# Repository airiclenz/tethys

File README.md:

<div align="center">

**A self-hosted, multi-channel automatic plant-watering system.**
</div>

Battery-powered wireless soil-moisture sensors report to a Raspberry Pi master
over a 2.4 GHz nRF24 radio link. The master decides when to water, drives the
pumps/valves, and serves a real-time web dashboard — all on your own LAN, no
cloud.

## Part 1 — What Tethys is and how to use it

### The big picture

Tethys has two kinds of hardware:

1. **Sensor nodes** (one per plant/pot, up to 5) — a battery-powered ATtiny84
   board with a capacitive soil-moisture probe and an nRF24L01+ radio. Each node
   sleeps almost all the time, wakes on a configurable interval, measures soil
   moisture and battery voltage, transmits a reading, and goes back to sleep.
   Designed to run for months on a single charge (~9 µA while sleeping).

2. **The master** — a Raspberry Pi with a custom HAT carrying the matching
   nRF24L01+ radio plus pump/valve driver outputs. The master listens for sensor
   readings, stores them, and when a channel's soil drops below its trigger
   threshold it runs that channel's pump (or opens its valve) for a configured
   duration. It also serves the web UI you use to configure and monitor
   everything.

```
   ┌─────────────┐   nRF24 2.4GHz      ┌──────────────────────────────────┐
   │ Sensor node │  (250kbps, 8-byte   │         Raspberry Pi master      │
   │  ATtiny84   │   versioned frames) │                                  │
   │  + moisture │ ◄──── reading ────► │  core daemon ─► pump/valve GPIO  │
   │  + nRF24    │      config ◄────   │              │                   │
   │  (battery)  │                     │  Django API (SQLite) ◄─► web UI  │
   └─────────────┘                     └──────────────┬───────────────────┘
        × up to 5                                     │  HTTP / WebSocket
                                                      ▼
                                              Your browser / phone
```

Each **channel** (1..5) pairs one sensor node with one pump or valve output.
A channel knows its soil-moisture trigger %, its pump run duration, and how
often its sensor should measure.

### Repository layout

```
tethys/
├── code/
│   ├── master/            # Everything that runs on the Raspberry Pi
│   │   ├── core/          # The watering daemon (radio + pump control + action engine)
│   │   ├── api/           # Django REST API (the system's database + state)
│   │   ├── web/           # Django + Channels dashboard (browser UI)
│   │   ├── camera/        # Optional on-demand webcam snapshot service (USB/V4L2)
│   │   ├── watchdog/      # Daily service-restart / log-vacuum job
│   │   ├── globals/       # Shared config + git-ignored secrets
│   │   └── install/       # install.sh, systemd units, nginx configs
│   └── sensor/            # Arduino/PlatformIO firmware for the sensor nodes (the "wpw" project)
├── hardware/              # KiCad schematics + Gerbers for the Pi HAT and the sensor PCB
├── graphics/              # Logos, hardware labels, web-UI assets, renders
└── docs/                  # Audits, protocol review, hardening notes, handoffs
```

### Hardware

**Master — Raspberry Pi + "WaterPlant Pi" HAT** (`hardware/rpi hat/`).
GPIO assignments live in [`code/master/core/hardware.py`](code/master/core/hardware.py):

| Function          | BCM pin(s)            | Notes                                            |
|-------------------|-----------------------|--------------------------------------------------|
| Channel outputs   | `16, 19, 20, 26, 21`  | One per channel; `CHANNEL_COUNT = 5`             |
| Shared pump pin   | `6`                   | Energised together with a channel in **valve** mode |
| Water-level sensor| `4`                   |                                                  |
| nRF24 CE / CSN / IRQ | `22 / 0 / 17`      | SPI radio                                         |
| Status LED / Fan  | `14 / 15`             |                                                  |

A channel of type **pump** drives its own pin directly. A channel of type
**valve** drives its pin *and* the shared `PUMP` pin (one pump pushing water
through whichever valves are open); the pump pin is reference-counted so it
only drops once the last valve closes.

**Sensor node — "Sensor" PCB** (`hardware/sensor/`), firmware in `code/sensor/`:

- **MCU:** ATmega/ATtiny84 @ 8 MHz (PlatformIO `TX` build), deep-sleep
  `SLEEP_MODE_PWR_DOWN`, woken by the 8-second watchdog timer.
- **Radio:** nRF24L01+ on CE=8 / CSN=9, 250 kbps, CRC-8, auto-ACK.
- **Moisture:** capacitive probe excited by a ~500 kHz square wave (Timer0 on
  `PB2`), read on ADC `PA3`; calibration min/max stored in EEPROM.
- **Battery:** monitored on `A7` against the internal 1.1 V reference; below
  **3.2 V** the node sends a battery-alert frame instead of a normal reading.

### Install (on the Raspberry Pi)

```bash
sudo apt install git -y
git clone https://github.com/airiclenz/tethys.git tethys
cd tethys/code/master/install
./install.sh
```

The installer updates the OS, creates a Python venv, installs Redis + nginx,
runs the Django migrations, registers the systemd services, enables SPI, and
**reboots** (re-run `./install.sh --rebooted=true` afterward if you decline the
auto-reboot). On first run it generates a random **API key** into the
git-ignored `code/master/globals/secrets.py` and **prints it** — copy it.

Useful flags:
- `--debug=true` — developer install (also installs the TypeScript toolchain).
- `--allowed-hosts=tethys.<tailnet>.ts.net` — extra `ALLOWED_HOSTS` for remote
  (VPN) access. Alternatively (and preferred per-install), list the name in the
  git-ignored `code/master/globals/allowed_hosts.py` (copy `allowed_hosts.example.py`)
  — no reinstall needed, just restart the services. See
  [`docs/remote-access-hardening.md`](docs/remote-access-hardening.md).

After it's up: open `http://<pi-host>/` in a browser → **Settings** (top menu) →
paste the API key → Save. The key gates **every** request (reads included; only
the CORS `OPTIONS` preflight is exempt), so the dashboard stays blank until it's
set. If a page can't authenticate (missing or wrong key), a warning banner
appears under the header with a link straight to Settings.

### Daily use

- **Sensor Readings page** (`/`) — per-channel reading history: two trend charts
  (moisture % and battery voltage over time) sit above a sortable table of the
  individual readings.
- **Channels page** (`/channels/`) — live moisture %, battery, last action per
  channel; enable a channel, set its nickname, type (pump/valve), pump duration,
  and the moisture trigger %; manually test a pump.
- **Schedules page** (`/schedules/`) — define **silent phases** (quiet hours):
  weekday + start time + duration windows during which *all* automatic watering
  is suppressed (e.g. overnight). The header shows a sleep icon while a silent
  phase is active.
- **Webcam page** (`/webcam/`) — *optional* live view from a USB camera. Off by
  default; flip **Enable** to refresh a snapshot every few seconds. Live-view
  only — nothing is recorded, and the camera releases automatically when you
  leave the tab or after an idle timeout. See *Webcam* below.
- **Order 66** (top menu) — recovery action for when a service or the Pi itself
  gets wedged: confirm the popup and the Pi performs a graceful reboot (back in
  ~1 minute). Gated by the API key, like pump control.
- The dashboard updates live over a WebSocket; no manual refresh needed.

### Webcam (optional)

Tethys can show a live webcam view on its own **Webcam** tab — handy for checking
on plants — but it ships **off** and only captures **on demand**:

- **USB camera (V4L2).** Plug in any UVC webcam; the service grabs JPEG snapshots
  with `v4l2-ctl` (no extra Python dependency). A Pi Camera Module (CSI) is not
  wired up yet — the capture code keeps a seam (`camera/captureBackend.py`) for
  adding it as one new class.
- **Snapshot-only, nothing recorded.** The tab fetches a fresh JPEG every few
  seconds (an authenticated `fetch`, gated by the same API key as everything
  else). There is no video stream and no storage — purely a live view.
- **Pick the size, view it full-screen.** A dropdown lists the resolutions the
  camera itself reports (so it isn't tied to one model), and the live frame can be
  expanded to fill the screen — both handy on a phone. The choice is per-session
  only; nothing is saved.
- **Focus & zoom sliders.** A plant sits at a fixed distance, so autofocus just
  hunts. The tab offers focus and zoom as sliders whose ranges are read from the
  camera itself — and a slider is disabled when the camera doesn't support that
  control. Setting focus pins it (no more hunting). Your pick is remembered in the
  browser; `CAPTURE_FOCUS` / `CAPTURE_ZOOM` in `camera/config.py` set the
  defaults a fresh browser starts from.
- **Fail-closed + auto-off.** The service boots disabled (a snapshot while off
  returns `409`). It auto-releases the camera after a short idle window and
  enforces a hard maximum on-time, mirroring the pump's auto-off safety — so the
  camera can never be left on by accident.
- **Least privilege.** `tethys-camera` runs as the normal app user (no root,
  unlike `tethys-core`), with only the `video` group added so it can open the
  `root:video` `/dev/video*` nodes. The installer adds the user to that group and
  installs `v4l-utils`.

### Updating / operating

From `code/master/install/`:
- `./installServices.sh` — re-deploy the systemd services from the current code.
- `./services-restart.sh`, `./services-stop.sh`, `./services-clearLogs.sh`.
- `./deploy-static.sh` — rebuild the frontend TypeScript and publish it to nginx.

The six services: `tethys-core`, `tethys-api`, `tethys-web`, `daphne`,
`tethys-watchdog` (restarts core+api+camera nightly at 01:00 and vacuums the
journal), and `tethys-camera` (the optional on-demand webcam, off by default).

### Firmware (sensor nodes)

Built with [PlatformIO](https://platformio.org/) from `code/sensor/`. Before
building, set the node identity in [`code/sensor/include/wpw_Config.h`](code/sensor/include/wpw_Config.h):
`SENSOR_NUMBER` (1–5). Flash with:

```bash
cd code/sensor
pio run -t program -e tethys-sensor     # via an AVR ISP programmer
```

> ⚠️ **The master and every sensor must be flashed together.** The wire format
> is versioned and fixed-size; a node on mismatched firmware fails the version
> check and goes silent (cleanly — it never corrupts data). See the
> *Known limitations / coordinated flash* note in [`CHANGELOG.md`](CHANGELOG.md).

### Sensor node LED — calibration & status blinks

A sensor node has no screen; its single onboard LED is how it talks to you.
Patterns are produced by `DoSimpleBlink(onMs, offMs)` and `DoSoftPulse(ms)`
([`code/sensor/src/wpw_Blinker.cpp`](code/sensor/src/wpw_Blinker.cpp); the soft
pulse is a software-PWM glow, since the LED pin has no free hardware PWM).

**How calibration works.** Calibration maps the probe's raw reading onto a
0–100 % moisture scale, and it is **two-point**: the node captures one reading in
a *wet* condition and one in a *dry* condition, then stores the lower value as
`MinimumValue` (wettest) and the higher as `MaximumValue` (driest) in EEPROM
(`Calibrate()` in [`code/sensor/src/wpw_Sensor.cpp`](code/sensor/src/wpw_Sensor.cpp)).
Later readings become `100 − map(raw, min, max, 0, 100)` %.

1. Trigger it from the web UI — set the channel's **calibrate** flag
   (`sensorTriggerCalibration`), then **power-cycle or reset the node**.
   Calibration runs only as part of the **boot-time** config exchange (the full
   `GETCONFIG` in `setup()`) — *not* on a normal measurement wake. A running node
   re-pulls its config periodically (see *Periodic config pull* below), but those
   pulls are deliberately **settings-only**: they carry measure-frequency /
   TX-power but never the calibration trigger, so they can't run calibration
   mid-life. The master delivers the trigger once and immediately clears the flag
   (`core/radio.py`), so if you set the flag while the node is already running,
   nothing happens until you reset it. (This is the usual reason a calibration
   "didn't start".)
2. The node then takes **two** measurements, each announced by the *calibration
   countdown* below (slow blinks → fast blinks → one long blink → it measures
   while the LED is off). Put the probe in one condition for the first capture
   and the other condition for the second.
3. **Order doesn't matter** — the firmware sorts the two readings into min/max.
   What matters is that the two conditions are genuinely different: if the two
   readings are too close, the calibration is **rejected** and the previous
   values are kept (signalled by the long 2 s blink).

**First reading after boot.** On every boot — including right after calibration —
the node waits ~1 minute (`STARTUP_SETTLE_SECONDS`, default 60, in
[`wpw_Config.h`](code/sensor/include/wpw_Config.h)) before taking and transmitting
its first reading. It *sleeps* through the wait (you'll see the heartbeat flash
each ~9 s), so it costs almost no power. Put the probe in its final monitoring
position before this window ends — the first reported value reflects wherever the
probe is at that moment, **not** the calibration captures.

**Periodic config pull.** A running node re-pulls its config so web-UI changes
(measure frequency, transmission power) reach it without a power-cycle. The cadence
is `PULL_CONFIG_CYCLE_SECONDS` in [`wpw_Config.h`](code/sensor/include/wpw_Config.h)
(default `3600` = 1 h; **`0` disables it** for maximum battery saving). To stay
gentle on the battery the pull **rides an existing measurement wake** — the radio
is already powered up, so it adds no extra power-up, and the master answers from
its warm `ConfigCache` so the listen window is usually a few milliseconds. The pull
therefore happens on the first measurement at/after the cycle has elapsed since the
last pull. These pulls are **silent** (no LED) and **settings-only** — they never
carry or clear the calibration trigger (calibration stays boot-only; see above).

The patterns, all on the sensor (TX) node LED:

| Event | Blink pattern | Meaning |
|-------|---------------|---------|
| **Power-on / node ID** | `N` slow blinks (150 ms on, 300 ms off), where `N` = `SENSOR_NUMBER` | Node booted and is powered; the count identifies which node it is (1–5). |
| **Config received** | a soft ~2 s glow (brightness ramps up then down) | The master answered the config request (at boot) and the settings were applied. |
| **No master reply** | two short flashes (15 ms) | Config request timed out (no answer within 500 ms); the node falls back to the settings stored in EEPROM. |
| **Config rejected** | three short flashes (15 ms) | The master replied but the frame failed the protocol-version / type check. |
| **Settings saved** | accelerating ramp — 150 → 100 → 75 → 50 → 25 → 15 ms — then one long 300 ms flash (ramps *up* to a strong finish) | New settings differed from EEPROM and were written. |
| **Settings unchanged** | decelerating ramp — 15 → 25 → 50 → 75 → 100 → 150 ms — fading out with no final flash (the mirror of *saved*) | Config was checked but nothing changed, so nothing was written. |
| **Heartbeat** | one very short flash (5 ms) each wake (~every 9 s) | Normal sleep/measure loop tick — the node is alive. |
| **Transmit failed** | four short flashes (15 ms) | The radio send failed; the node backs off (~15 min) before retrying. Part of the short-flash radio-error family, counted: 2 = no reply, 3 = bad frame, 4 = send failed (a *successful* config exchange is the soft glow above instead). |
| **Calibration countdown** | 10 slow blinks (300 ms) → 20 fast blinks (100 ms) → one long blink (1 s) → LED off while it measures | Counts down to a calibration capture. Runs **twice**, once per measurement point. |
| **Calibration rejected** | one very long flash (2 s) | The two calibration readings were too close together; calibration was discarded and the previous values kept. |

---

## Part 2 — Orientation for a contributor or coding agent

This half is the lightweight `CLAUDE.md`: the runtime topology, the invariants
that are easy to break, and where to look. Read it before changing anything on
the master.

### Process & port map

Everything runs on the Pi as systemd services (units in
`code/master/install/assets/*.service`, nginx in `*.nginx`):

| Service           | Process                         | Binds        | Reached via            |
|-------------------|---------------------------------|--------------|------------------------|
| `tethys-core`     | `core/tethys_core.py` (asyncio) | — (GPIO/radio) | n/a                  |
| `tethys-api`      | gunicorn → `tethys_api.wsgi`    | `localhost:5001` | nginx **:5000**    |
| `tethys-web`      | gunicorn → `tethys_web.wsgi`    | `localhost:8000` | nginx **:80** `/`   |
| `daphne`          | ASGI → `tethys_web.asgi`        | `0.0.0.0:8001`   | nginx **:80** `/ws/`|
| `tethys-watchdog` | `watchdog/tethys_watchdog.py`   | —            | nightly restart        |
| `tethys-camera`   | `camera/tethys_camera.py` (stdlib HTTP) | `127.0.0.1:8002` | nginx **:80** `/camera/` |
| redis-server      | Channels layer for daphne       | `localhost:6379` | —                  |

**The API is the single source of truth.** Both the core daemon and the web
backend treat it as the database boundary and reach it at `http://localhost:5000/api/`
(nginx → gunicorn:5001). It is Django REST Framework over **SQLite**
(`api/db.sqlite3`).

### Data flow (one reading → one watering)

1. A sensor wakes, measures, and transmits a 7-byte frame on its pipe.
2. `core/radio.py` (`checkRadioInbox` → `handlePayload`) drains the RX FIFO,
   validates each frame via `core/protocol.py`, and `POST`s the reading to
   `sensorData/`. On success it sets that channel's flag in
   `core/config.py::FlagHandler.channelFlags`.
3. `core/actionEngine.py::handleActions` (called each core-loop pass) checks the
   **silent phase** first (fail-closed — see below), then for each flagged
   channel pulls `channelSummary/<n>` and, if `moisture <= trigger` and the
   channel is enabled, calls `pumpController.run_pump(...)`.
4. `core/pumpController.py` energises the line, arms a `threading.Timer`
   auto-off, and on completion writes an `actionLog/` entry — all non-blocking,
   so the radio keeps listening while a pump runs.
5. The web UI sees the change: `web/tethys_web/jobs.py` polls the API every 10 s
   (`/lastUpdate/`, `/channelSummary/`, `/schedule/`, `/silentPhaseStatus/`) and,
   on a change, broadcasts to all browsers over the `/ws/tethys/` WebSocket
   (`web/tethys_web/consumers.py`).

A **manual *Test Channel* tap** uses the same hardware path, not a separate one:
the API enqueues a `ManualCommand` (it never drives GPIO), the core drains it each
loop pass and runs it through the same `pumpController` (rejecting an activate when
another channel is already running), and writes the outcome back for the UI to
poll. This is what keeps the one-channel power limit holding for manual control —
see *Invariants* below.

When a sensor asks for its config (`GETCONFIG`), the master answers from an
in-memory `ConfigCache` (warmed out-of-band by `Radio.refreshConfigCache`), never
with a blocking HTTP call inside the sensor's short listen window. A running node's
periodic, settings-only pull (`GETCONFIG_PERIODIC`) is answered the same way but
with the calibration trigger stripped and never cleared.

### Invariants — break these and something physical or silent goes wrong

- **Pump safety.** Every "pump on" is clamped to `MAX_PUMP_SECONDS = 300` and has
  a guaranteed off (timer + `try/finally`). The controller drives all lines LOW
  on construction (fail-safe boot) and on `SIGTERM`/`atexit`. Never reintroduce a
  watering path that bypasses `pumpController`. `make_controller()` is the *only*
  place `lgpio` is bound; all hardware goes through the `GpioAdapter` seam so the
  logic is testable without a Pi.
- **One channel at a time (power limit).** `pumpController` is the *single owner*
  of the watering GPIO. Both automatic watering and the web UI's manual *Test
  Channel* taps go through it — the latter via the `ManualCommand` queue the core
  drains each loop pass — so its `max_concurrent = 1` guard holds the invariant
  that **at most one channel (plus the shared pump pin) is ever energised**, which
  protects the power supply. A manual activate that arrives while another channel
  is running is *rejected*, not run. The API process never drives GPIO itself.
- **Silent phase is fail-closed.** If the API is unreachable, `isInSilentPhase()`
  returns `None` and `actionEngine` **skips watering** for that pass — it must
  never water on unknown state. The window math lives in
  `api/tethys_api/silentphase.py` (stdlib-only, unit-tested independently of
  Django).
- **Timezones.** `globals/config.py::TIME_ZONE` (`Europe/Stockholm`) is the
  single deployment/display zone, shared by `core` and `web`. The **Django API
  deliberately keeps `TIME_ZONE = 'UTC'` as its storage zone** — schedule start
  times are wall-clock times-of-day stored on a placeholder date; the deployment
  zone is applied only at silent-phase evaluation. Don't "fix" the API to local
  time. (See the silent-phase fixes in `CHANGELOG.md` for why.)
- **Wire protocol is versioned and fixed-size.** `core/protocol.py` and
  `sensor/include/wpw_RXTX.h` / `wpw_Config.h` must stay byte-for-byte in sync:
  `PROTOCOL_VERSION = 1`, `PAYLOAD_SIZE = 8`, structs `<BBBf>` (sensor→master, 7 B)
  and `<BBHB?>` (master→sensor, 6 B). Bump `PROTOCOL_VERSION` on *any* layout
  change — and re-flash everything (no backward compat). Adding a new *message
  type* (the type byte, e.g. `DATATYPE_CMD_GETCONFIG_PERIODIC = 8`) is **not** a
  layout change, so it does not bump the version; keep the type constants in sync
  on both ends. An un-updated peer ignores an unknown type (the sensor's periodic
  pull just times out and retries), so mixed versions degrade gracefully.
- **Pipe 0 is reserved.** Channels map 1:1 onto nRF24 reading pipes 1..N; pipe 0
  is the ACK/writing address. This caps the link at 5 sensors. See
  `protocol.pipe_for_channel`.
- **`CHANNEL_COUNT` is the single source of truth** (`= len(Pins.CHANNELS) = 5`).
  The DB/radio reference 6 channels historically; a 6th needs a physical GPIO pin
  first. Don't hardcode channel counts.
- **Secrets.** `globals/secrets.py` (git-ignored) holds `TETHYS_API_KEY`,
  `API_SECRET_KEY`, `WEB_SECRET_KEY`, and is read by *both* the Django apps and
  the non-Django core. Template: `globals/secrets.example.py`. Every API request
  needs `X-API-Key` (reads included; only CORS `OPTIONS` is exempt) — see
  `api/tethys_api/permissions.py::ApiKeyRequired`.

### Auth posture

A single shared API key gates **all** requests, compared constant-time,
fail-closed. The core (`apiInterface.py`, `radio.py`) and the web backend
(`jobs.py`, `tools.py`) send it server-side; the browser stores it in
`localStorage` and `common.ts` injects it into every fetch. Transport is plain
HTTP on the LAN — for remote access, front it with a VPN overlay (Tailscale/
WireGuard), not an open port. See [`docs/remote-access-hardening.md`](docs/remote-access-hardening.md).

### Data model (Django, `api/tethys_api/models.py`)

- **Channel** (`number` PK) — `enabled`, `nickName`, `channelType` (pump/valve),
  `actionTriggerPercent`, `pumpDurationSeconds`, `sensorMeasureFrequencyMinutes`,
  `sensorTriggerCalibration`, `sensorTransmissionPowerLevel`.
- **SensorData** — `channel` FK, `moisturePercent`, `batteryVoltage`, `timestamp`.
- **ActionLog** — `channel` FK, `actionType`, `startTime`, `endTime`.
- **Schedule** — `weekday`, `scheduleType` (`silent`), `startTime` (UTC wall-clock),
  `durationMinutes`, `enabled`.
- **ManualCommand** — `channel` FK, `action` (activate/deactivate), `status`,
  `message`, `requestedAt`, `processedAt`. The web UI enqueues a manual *Test
  Channel* tap here; the core drains it through `pumpController` (the API never
  drives GPIO) and reports the outcome back for the UI to poll.
- Lookup tables: `ChannelType`, `ActionType`, `ScheduleType`, `TransmissionPowerLevel`.
- `channelSummary/<n>` is the denormalized read both the core and UI consume
  (channel config + latest sensor reading + counts).

### Tests

**Backend (core + API)** — pure Python, no Pi/hardware needed:

```bash
cd code/master
pip install -r install/python-requirements-dev.txt   # pytest, dev-only
pytest                                                # pytest.ini sets paths
```

Covers the parts that gate physical action or silent failure: `core/tests/`
(pump controller, GPIO adapter, protocol framing, action engine, manual-command
queue) and `api/tethys_api/tests/` (API-key permission, silent-phase window math,
`LAST_DATA_UPDATE` wiring, manual-command lifecycle). All run without `lgpio`/`pyrf24`/a Pi, thanks to the
GPIO and protocol seams. **Add tests behind those seams when you touch the
watering, radio-framing, or silent-phase paths.**

The camera service has its own pure-Python suite (`camera/tests/`: the
fail-closed snapshot gate, idle / max-on auto-off, and the X-API-Key check, via
`FakeSnapshotBackend`). It is not in the default `testpaths`, so run it
explicitly: `pytest camera/tests`.

**Web UI (Playwright)** — browser-driven regression tests for the channels UI:

```bash
cd code/master/web
pip install -r requirements-dev.txt
playwright install --with-deps chromium   # downloads Chromium + apt libs (needs sudo)
pytest
```

These drive a headless Chromium against a throwaway Django live server, exercising
the real compiled JavaScript (`conftest.py` compiles `static/ts` → `static/js`
first), so they catch DOM/click-handler bugs the Python suites can't. See
[`web/tests/README.md`](code/master/web/tests/README.md) for what's covered and how
it works. A developer install (`install.sh --debug=true`) installs all of the above
automatically.

### Frontend build

TypeScript sources in `web/static/ts/` compile to `web/static/js/` via
`compile.sh` (`tsc`) / `compileAutomatically.sh` (watch). The build is strict
(`strict: true` in `tsconfig.json`) and `tsc -p tsconfig.json` compiles cleanly.
Use `install/deploy-static.sh` to compile + publish to the nginx static dir. The
compiled `web/static/js/` is git-ignored — it is rebuilt from the `.ts` sources on
deploy and before the UI tests, so the TypeScript is the single source of truth.

> ⚠️ **Editing the frontend? Change the `.ts` files in `web/static/ts/`, never
> `web/static/js/` directly.** The `.js` folder is generated output (git-ignored)
> and is overwritten on every `tsc` run / deploy, so any hand-edits to the `.js`
> are silently lost. Tip: `git check-ignore <path>` will tell you if a file is a
> build artifact before you touch it.

### Known limitations / deferred (see `CHANGELOG.md` + `docs/`)

- Low-battery flag is logged but not persisted (no `SensorData` column yet).
- Webcam is live-view only — no recording / clip storage, snapshot download, or
  multiple cameras; the CSI/`picamera2` backend is deferred (seam left in
  `camera/captureBackend.py`).

### Where the design rationale lives

`docs/audits/` (code audit, architecture review, protocol review) and
`docs/handoffs/` capture *why* the current shape exists — the pump-safety module,
the API-key lockdown, the protocol hardening, and the silent-phase timezone fixes.
`CHANGELOG.md` is the readable summary of each. Start there before reworking any
of the invariants above.

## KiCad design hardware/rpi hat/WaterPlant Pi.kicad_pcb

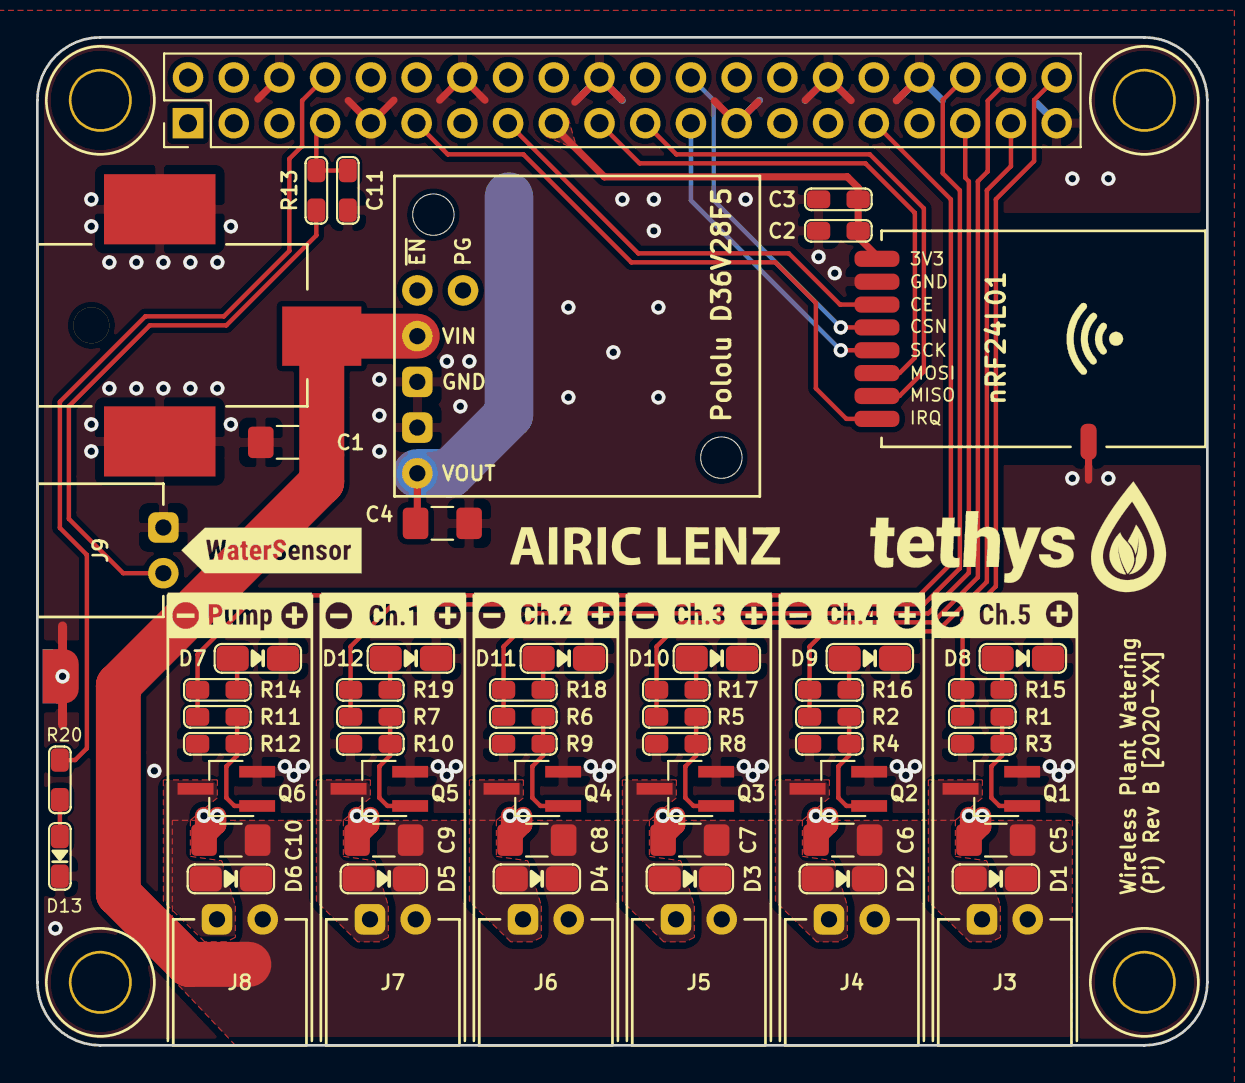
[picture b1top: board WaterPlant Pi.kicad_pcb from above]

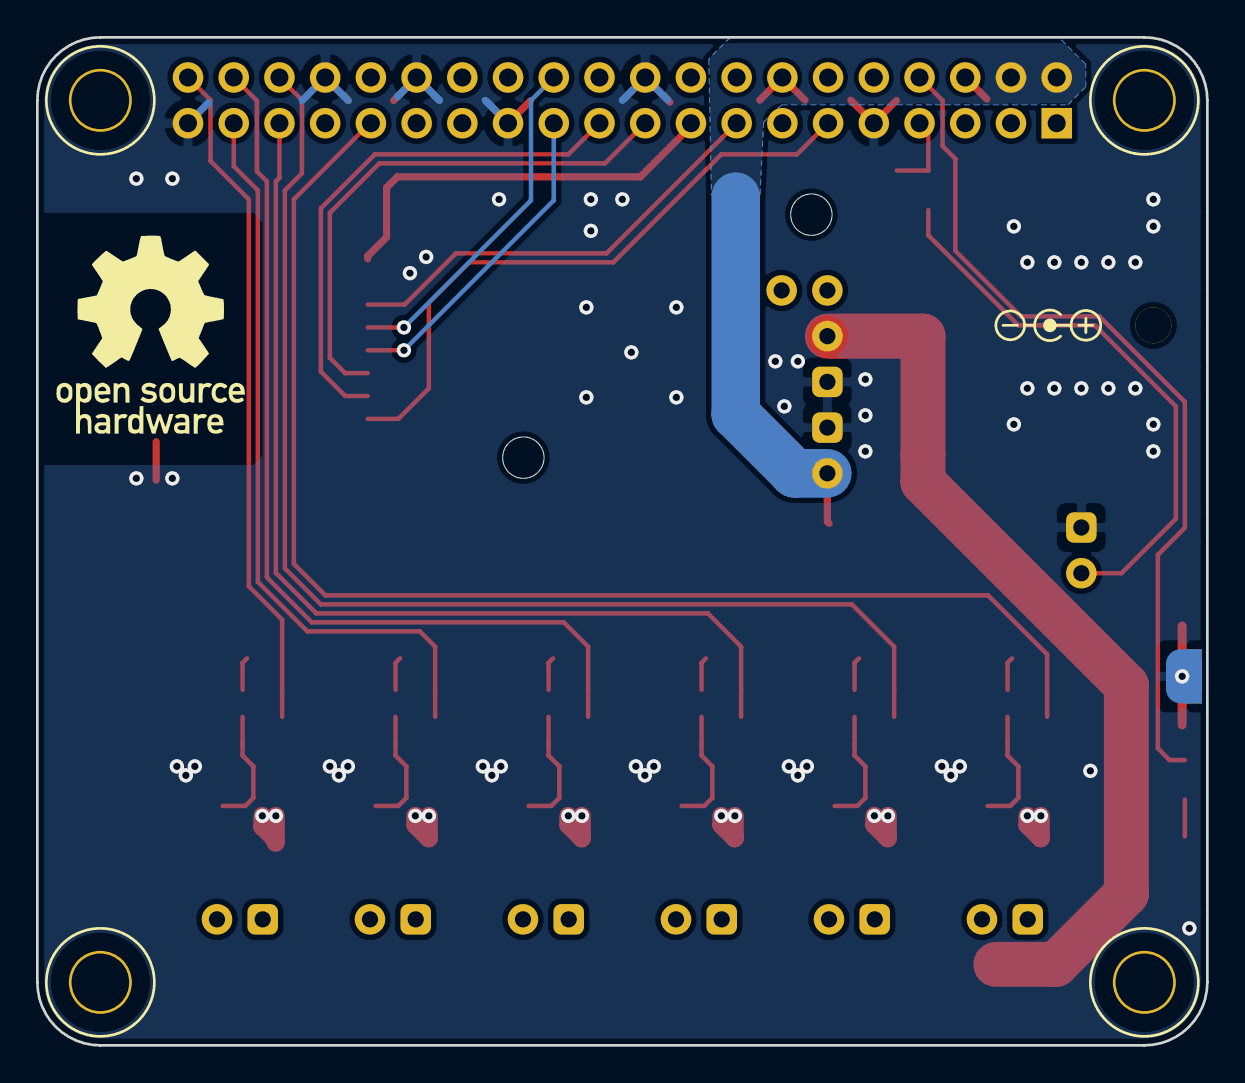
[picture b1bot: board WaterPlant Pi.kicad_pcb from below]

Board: 2 copper layers, 65.0 x 56.0 mm, 69 parts (2 on the bottom side), 38 nets.

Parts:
BatteryPolaritySign: VAL**; Logo_BatteryPolarity
C1, C4, C5, C6, C7, C8, C9: 10uF 50V; C_1206_3216Metric_Pad1.42x1.75mm_HandSolder
C2: 0.1uF 16V; Device_0603_Handsoldering
C3, C11: 1uF 16V; Device_0603_Handsoldering
C10: 10uF 25V; C_1206_3216Metric_Pad1.42x1.75mm_HandSolder
D1, D2, D3, D4, D5, D6: Schottky 2A; Diode_0805_HandSoldering
D7, D8, D9, D10, D11, D12: LED_Small; Diode_0805_HandSoldering
D13: LED_Small; Diode_0603_Handsoldering
DR1, DR2, DR3, DR4: Drill_Hole; Hole_M3_NPTH_Mounting
J1: Conn_02x20_Odd_Even; PinHeader_2x20_P2.54mm_Vertical
J2: Barrel_Jack; POWER_JACK_2.1_SMD
J3, J4, J5, J6, J7, J8, J9: Conn_01x02_Female; Connector_JST_XH_02x01_angeled
L1: Logo_OSH; Logo_OSHW_Silk_10mm
Logo1: Logo_Airic_Lenz; Logo_AiricLenz_Silk_15mm
MOD1: Module_nRF24L01; Module_nRF24L01_SMD
Q1, Q2, Q3, Q4, Q5, Q6: DMG3418L; TSOT-23_HandSoldering
R1, R2, R5, R6, R7, R11: 470Ω; Device_0603_Handsoldering
R3, R4, R8, R9, R10, R12: 10kΩ; Device_0603_Handsoldering
R13, R14, R15, R16, R17, R18, R19, R20: 1kΩ; Device_0603_Handsoldering
TP1: TESTPOINT; Testpoint_GND
U1: Module_Pololu_D36V28F5; Module_Pololu_5V_D36V28F5

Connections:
+3V3: C2.2, C3.2, J1.1, J1.17, MOD1.1
+5V: C4.1, J1.2, J1.4, U1.1
+12V: C1.1, C5.1, C6.1, C7.1, C8.1, C9.1, C10.1, D1.1, D2.1, D3.1, D4.1, D5.1, D6.1, J2.1, J3.2, J4.2, J5.2, J6.2, J7.2, J8.2, U1.4
GND: C1.2, C2.1, C3.1, C4.2, C5.2, C6.2, C7.2, C8.2, C9.2, C10.2, C11.1, D7.1, D8.1, D9.1, D10.1, D11.1, D12.1, D13.1, J1.6, J1.9, J1.14, J1.20, J1.25, J1.30, J1.34, J1.39, J2.2, J9.1, MOD1.2, Q1.2, Q2.2, Q3.2, Q4.2, Q5.2, Q6.2, R3.2, R4.2, R8.2, R9.2, R10.2, R12.2, TP1.1, U1.2, U1.3
GPIO_4_WATER: C11.2, J1.7, R13.2
GPIO_06_PUMP: J1.31, R11.2, R14.1
GPIO_08_CSN: J1.24, MOD1.4
GPIO_09_MISO: J1.21, MOD1.7
GPIO_10_MOSI: J1.19, MOD1.6
GPIO_11_SCK: J1.23, MOD1.5
GPIO_14_LED: J1.8, R20.2
GPIO_16_CH1: J1.36, R7.2, R19.1
GPIO_17_IRQ: J1.11, MOD1.8
GPIO_19_CH2: J1.35, R6.2, R18.1
GPIO_20_CH3: J1.38, R5.2, R17.1
GPIO_21_CH5: J1.40, R1.2, R15.1
GPIO_22_CE: J1.15, MOD1.3
GPIO_26_CH4: J1.37, R2.2, R16.1
unnamed: D1.2, J3.1, Q1.3
unnamed: D2.2, J4.1, Q2.3
unnamed: D3.2, J5.1, Q3.3
unnamed: D4.2, J6.1, Q4.3
unnamed: D5.2, J7.1, Q5.3
unnamed: D6.2, J8.1, Q6.3
unnamed: D7.2, R14.2
unnamed: D8.2, R15.2
unnamed: D9.2, R16.2
unnamed: D10.2, R17.2
unnamed: D11.2, R18.2
unnamed: D12.2, R19.2
unnamed: D13.2, R20.1
unnamed: J9.2, R13.1
unnamed: Q1.1, R1.1, R3.1
unnamed: Q2.1, R2.1, R4.1
unnamed: Q3.1, R5.1, R8.1
unnamed: Q4.1, R6.1, R9.1
unnamed: Q5.1, R7.1, R10.1
unnamed: Q6.1, R11.1, R12.1

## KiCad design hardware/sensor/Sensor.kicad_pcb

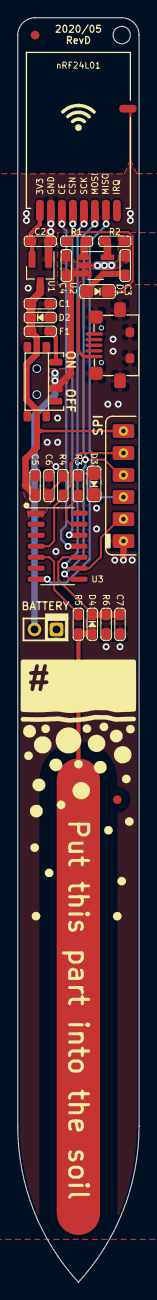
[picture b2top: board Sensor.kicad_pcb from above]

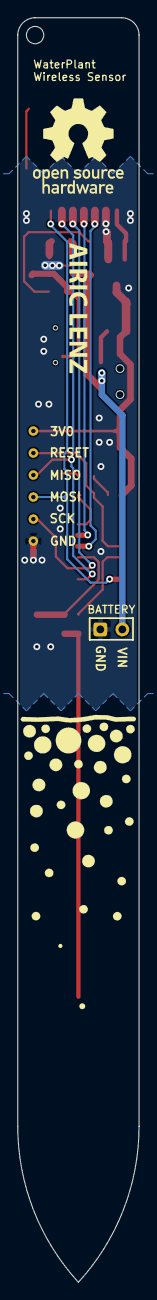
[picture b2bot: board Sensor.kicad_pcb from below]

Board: 2 copper layers, 14.0 x 145.9 mm, 32 parts (2 on the bottom side), 20 nets.

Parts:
C1, C2, C6, C7: 1u; Device_0603_Handsoldering
C3, C4: 4.7uF; Device_0603_Handsoldering
C5: 0.1u; Device_0603_Handsoldering
C8: C_Soil; WaterPlant_C_Soil
D1: LED_BLUE; LED_0805_Handsoldering
D2, D4: D_Small; Diode_0603_Handsoldering
D3: LED_RED; LED_0805_Handsoldering
DR1: Drill_Hole; Hole_M2_NPTH
F1: JK-SMD0603-005; Device_0603_Handsoldering
FID1, FID2: Fiducial
J1: BatteryConnector; Connector_PinHeader_02x1
J2: PowerSwitch; Switch_SMD_K3-1296S-E2
J3: USB_B_Micro; Connector_USB_Micro_B_C77238
J4: Conn_01x06_Female; Connector_FlatHeader-06x1_SPI
L1: Logo_OSH; Logo_OSHW_Silk_10mm
Logo1: Logo_Airic_Lenz; Logo_AiricLenz_Silk_15mm
MOD1: nRF24L01; Module_nRF24L01_SMD
R1, R2, R3: 2k; Device_0603_Handsoldering
R4, R5: 10k; Device_0603_Handsoldering
R6: 510k; Device_0603_Handsoldering
U1: MCP1700-3002E_SOT23; SOT-23_Handsoldering
U2: MCP73831-2-OT; SOT-23-5_HandSoldering
U3: ATtiny84-20SSU; SOIC-14_3.9x8.7mm_P1.27mm

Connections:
+3V0: C2.2, MOD1.1, U1.2
+5V: C3.1, D1.2, J3.1, U2.4
D2_CLKOUT: R5.1, U3.5
D4_A6_MOSI_SDA: J4.3, MOD1.7, U3.7
D5_A5_MISO: J4.4, MOD1.6, U3.8
D6_A4_SCK_SCL: J4.2, MOD1.5, U3.9
D7_A3_CAPACITANCE: C7.1, D4.1, R6.2, U3.10
D8_A2: MOD1.3, U3.11
D9_A1: MOD1.4, U3.12
GND: C1.2, C2.1, C3.2, C4.2, C5.2, C6.2, C7.2, D2.2, D3.1, J1.1, J3.5, J3.6, J4.1, MOD1.2, R2.1, R6.1, U1.1, U2.2, U3.14
unnamed: C8.1, D4.2, R5.2
unnamed: D1.1, R1.2
unnamed: D3.2, R3.1
unnamed: F1.2, J2.3
unnamed: R1.1, U2.1
unnamed: R2.2, U2.5
unnamed: R3.2, U3.13
RESET: J4.5, R4.2, U3.4
VBAT: C4.1, J1.2, J2.2, U2.3
VCC: C1.1, C5.1, C6.1, D2.1, F1.1, J4.6, R4.1, U1.3, U3.1

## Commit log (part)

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2024-07-16 additional work on the new api
2024-07-17 removed api migrations from tracking
2024-07-18 Schedules working with the new API
2024-07-19 Update views.py for plural schema names
2024-07-19 web.schedules and api fully working now
2024-07-19 fixed a bug with schedule .starttime updates
2024-07-20 status quo reached - frogress from here on
2024-08-01 move of web to new folder structure
2024-08-03 added core service code
2024-08-03 updated api settings
2024-08-03 update of runserver scripts
2024-08-03 added migrations to install script
2024-08-04 moved arduino code and other resourced into this repo
2024-08-10 radio communicatin working now without IRQ
2024-08-10 communication with new Pi working (sensor update)
2024-08-11 removing migrations from git tracking
2024-08-11 made gitignore more better
2024-08-11 cleanup of core-code
2024-08-12 initial script version for service installation is working
2024-08-12 latest update for install script
2024-08-13 Websocket is working now; Adjusted install script accordingly;
2024-08-13 added logos
2024-08-14 added reboot to install script, better logging in install script;
2024-08-14 cleanup and better logging
2024-08-14 install script improvements (added npm, tsc)
2024-08-15 better support and installation scripts
2024-08-15 better logging in the api
2024-08-16 minor update of the service-restart script
2024-08-20 added fan controller code
2024-08-20 fixed a big with websocket updates of the channel settings
2024-08-20 added version to the api; initial refactoring for globals module
2024-08-20 fixed a bug in the core with asyncio; improved service restart script;
2024-08-21 added 6th channel to master
2026-06-13 Implement code changes to enhance functionality and improve performance
2026-06-13 Archive API key documentation for mutating endpoints (audit #3)
2026-06-14 Add note to preserve sensor calibration across re-flashes in TODO
2026-06-15 chore: remove outdated documents and handoffs
2026-06-15 Ignore local-only docs/ directory
    Handoffs, audits, and plans under docs/ are working notes kept on the
    machine, not part of the tracked codebase.
2026-06-15 Add OpenAPI docs via drf-spectacular
    Wire up drf-spectacular to expose an auto-generated OpenAPI schema plus
    Swagger UI and ReDoc for the master API:
    - /api/schema/ - OpenAPI 3 schema
    - /api/docs/ - Swagger UI
    - /api/redoc/ - ReDoc
    The doc endpoints are served with AllowAny so the schema and the UIs that
2026-06-15 bugfix: Add api-key requirements for drf-spectacular schema views
2026-06-15 Refactor deploy-static.sh to restart all services and improve output messages
2026-06-15 Fix non-functional 'add new channel' button and auto-open new channel
    The add-channel button silently did nothing. addNewChannel() POSTed a body
    with 'triggerLevel: 50', but the Channel model/serializer field is the
    required 'actionTriggerPercent', so the API returned 400 and the handler
    bailed on !response.ok.
    Fixing that exposed a second bug: on success the code did
    parseInt(responseBody), but the POST returns the full channel JSON, not a
2026-06-15 Add moisture and battery-voltage trend charts to Sensor Readings
    The Sensor Readings page now shows two time-series line charts (moisture %
    and battery voltage over time) side by side above the readings table, drawn
    from the data the page already loads.
    - charts.ts (tethys.charts): renders both charts for the selected channel,
    updates in place on channel change / delete, clears when empty. Moisture
    y-axis fixed 0-100%; voltage y-axis auto with a dashed 3.5 V reference line;
2026-06-16 Fix sparse-channel settings crash; add click-outside-to-deselect
    Channel settings looked channels up with channels[number - 1], assuming
    the array index matched the channel number. With non-contiguous channels
    (e.g. 1, 2, 5) opening or editing channel 5's settings threw 'undefined
    is not an object'. Route every lookup through getIndexOfchannelWithNumber(),
    which now finds the entry by its .number instead of subtracting 1. Also
    fix updateNickName() comparing the new name against .enabled rather than
2026-06-16 Document web UI tests; install test tooling in dev install
    - README: split Tests into backend + web UI (Playwright) blocks; note that
    compiled static/js is git-ignored and rebuilt from .ts.
    - CHANGELOG: add [Unreleased] entries for the sparse-channel settings crash
    fix + click-outside-to-deselect, and the Playwright UI test harness +
    untracking of compiled JS.
    - install.sh: --debug=true now also installs the dev/test tooling (pytest,
2026-06-16 Add auth-failure banner on page load
    Every API request needs an X-API-Key; a missing or wrong key gets a 403,
    so without the key the dashboard silently failed to load any data. On page
    load afterPageLoad() now probes the cheapest endpoint (GET /api/version/):
    a 403 shows a dismissible warning banner under the header linking to
    Settings, and saving a correct key re-probes and clears it.
    Also corrects the README setup paragraph: the key gates every request
2026-06-16 Even out measurements/actions table column widths; align headers with rows
    - Measurements: four data columns at col-25 + col-2 delete column (header + rows).
    - Actions: five data columns at col-20 + col-2 delete column (header + rows).
    - Add a hidden 42px spacer in each header's delete cell to match the row button width.
    - Add a .col-1 flex-basis helper.
2026-06-16 Bump version to 3.0.0
2026-06-16 Make daphne restart fast: daemon poll thread + capped stop timeout
    The WebSocket poll thread (RepeatTimer in jobs.py) was non-daemon and never cancelled, so on SIGTERM CPython blocked joining it until systemd's 90s stop timeout SIGKILLed daphne, stalling every deplo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
    Backstop: cap daphne.service TimeoutStopSec at 5s so a future shutdown hang can't cost 90s again (a healthy graceful stop measures ~0.6s; SIGKILL is safe here since state lives in the DB/Redis/core a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
2026-06-17 Keep table headers aligned with rows when the frame narrows
    Table cells are flex items whose .col-* classes set only flex-basis,
    leaving the default min-width:auto. That floors each cell at its own
    content width, so the wider header labels stopped shrinking while the
    shorter-content body columns kept going, drifting out of alignment in
    the fluid range above the 700px cards breakpoint.
    Add min-width:0 to the data columns (.col-2 delete column excluded so
2026-06-17 Fix mangled site footer in phone mode
    Stack each footer readout label over its value (Pi-Core: / 42.8°C) at all
    widths by composing the strings with a <br>, in common.ts and the layout.html
    placeholders.
    On phone (<=700px) rebuild the footer as a clean flex line: hide the tagline and
    the layout-only spacer columns, let the two readouts size to content and sit
    left with a gap, push the OSH logo to the right edge with margin-left:auto, and
2026-06-17 Fix phone-width horizontal scroll from off-screen tooltip and bare chart canvas
    The empty strip on the right edge at phone width (and its horizontal
    scrollbar) came from the shared header, not the modal pop-ups (those are
    position:fixed and add no scroll width):
    - The silent-phase tooltip (.tooltiptext) is position:absolute, width:270px,
    anchored near the top-right of the header. With no offset it grew rightward,
    off-screen, so even while visibility:hidden it laid out and extended the
2026-06-17 Wire "Order 66" menu to a key-gated graceful Pi reboot
    The Order 66 popup linked to a non-existent /shutdown route (404). It now triggers POST /api/reboot/ — a key-gated, POST-only endpoint that runs a graceful `systemctl reboot`, deferred via a detached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
2026-06-17 Fix intermittent nginx 502 / lost /channels redirect from IPv6 localhost upstreams
    proxy_pass targeted the name 'localhost', which resolves to both 127.0.0.1 and ::1, while gunicorn (web :8000, api :5001) and daphne (:8001) bind IPv4 only. nginx round-robined onto [::1], got connec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
2026-06-18 Enforce "one channel + pump at a time" for manual Test Channel taps
    The web "Test Channel" toggle drove watering GPIO directly through core/channel.setOutputState, bypassing the PumpController that owns the max_concurrent=1 guard. Because the API runs 3 gunicorn work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
    Make the core PumpController the single owner of watering GPIO. The API now enqueues a ManualCommand row instead of touching GPIO; the single core process drains pending commands each loop pass and r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
2026-06-18 Source OpenAPI docs version from globals/config.py
    SPECTACULAR_SETTINGS['VERSION'] was a hardcoded '3.0.0' literal that had to
    be hand-bumped every release. Import the version from globals/config.py --
    the same Version object GET /api/version/ already serves -- and stringify it
    for the OpenAPI info.version field, so the docs version can never drift from
    the release version.
2026-06-18 Show version in web footer, sourced from globals/config.py
    The footer carried no version, and the only web version literal lived in the
    About dialog. Add a context processor (tethys_web.context_processors.app_version)
    that exposes str(config.version) as {{ tethys_version }} to every template, and
    render it in both the footer brand line and the About dialog. The web app now
    has no hardcoded version literal -- both spots track the release version from
    the single source of truth automatically.
2026-06-18 Webcam: device-derived capture resolution + full-screen view
    The Webcam tab captured at a fixed 1280x720 and had no way to view the live
    frame full-screen. Resolution is now selectable from a dropdown the client
    fills from the camera itself (so it isn't tied to one model), and the frame
    can be expanded to fill the viewport -- both aimed at phone-width viewing.
    Both are in-session only; nothing is persisted or recorded, and capture stays
    one-shot (resolution is a per-request parameter, no device restart).
2026-06-18 Webcam: focus/zoom sliders read from the camera (+ keep-alive, frame counter)
    Focus/zoom offered as live sliders whose ranges are read from the camera
    (v4l2-ctl --list-ctrls, fail-soft); a slider is disabled for a control the
    camera doesn't expose, and a pick is remembered per-device. The snapshot
    request carries ?focus=&zoom= (range-validated -> 400) and is applied per grab.
    Manual focus is now actually honored. Two C200 quirks (verified on hardware):
    the camera resets focus_absolute when a stream stops, and its focus motor only
2026-06-18 Webcam: USB-drop auto-recovery (watchdog + Reset button)
    The Anker C200 occasionally EPROTO-crashes mid-session and disconnects;
    once it's off the bus only a USB host-controller re-enumeration brings it
    back (a service restart cannot). Recover it without a physical replug via
    two paths into globals/usb_recovery.py:
    - Watchdog auto-heal: tethys_watchdog checks the bus every minute and
    re-enumerates a missing camera, rate-limited by exponential back-off so
